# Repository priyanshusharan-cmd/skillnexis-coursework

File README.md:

# SkillNexis Coursework

One repository for all 26 enrolled subjects. Each subject has its own folder, with work grouped under `week-1/` or `week-2/` as available. Course names use lowercase slugs for readable paths.

## Subjects

| Course | Folder |
|---|---|
| C Programming | `c-programming/` |
| C++ Programming | `cpp-programming/` |
| Python Programming | `python/` |
| Java Programming | `java/` |
| Web Development | `web-development/` |
| Full Stack Web Dev (MERN) | `mern/` |
| Data Science with Python | `data-science-python/` |
| Machine Learning & AI | `machine-learning-ai/` |
| Data Structures & Algorithms | `dsa/` |
| Mobile App Dev (Flutter) | `flutter/` |
| Cloud Computing with AWS | `aws-cloud/` |
| Data Analyst | `data-analyst/` |
| Power BI | `power-bi/` |
| Game Developer (Android & iOS) | `game-development/` |
| Software QA Tester (Bug Hunter) | `qa-testing/` |
| UI/UX Designer | `ui-ux/` |
| Digital Marketing | `digital-marketing/` |
| Video Editor & Content Creator | `video-editing/` |
| IoT with AI | `iot/` |
| IoT & C Embedded Programming | `iot-c-embedded/` |
| Educational Content Creator Intern | `educational-content-creator/` |
| 3D Modeling & CAD for Simulation | `3d-cad-design/` |
| AI Automation Engineer | `ai-automation/` |
| Software Engineer | `software-engineer/` |
| Deep Learning & AI | `deep-learning/` |
| Generative AI & LLMs | `generative-ai-llm/` |

## Week 1 status and evidence

Week 1 source packs were available for 20 distinct subjects. The Data Science download duplicated the Data Analyst pack, so its folder labels that source limitation. The other five folders were prepared from their Week 1 requirements on the course site. No downloaded lecture bundles are copied into this repository.

Some deliverables require an environment or evidence that was not available during preparation: AWS account/bucket activity, IoT hardware, a Unity or Flutter build, video footage/export, Figma files, a live demo-site bug report, 3D renders/exports, and model evaluation outputs. Those folders include source, plans, or templates and clearly identify evidence that still needs to be collected. Synthetic datasets are labeled as such. No run or result is claimed unless its evidence is included.

C Programming and Python also contain Week 2 folders from earlier work. Other courses currently contain Week 1 only.

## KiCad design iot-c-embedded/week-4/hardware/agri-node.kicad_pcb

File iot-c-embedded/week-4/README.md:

# IoT & C Embedded Programming — Week 4: Smart Agriculture System (Major Project)

An ESP32 node that watches soil moisture, temperature and light, waters plants through a pump, reports over MQTT, sleeps most of the time to run on one 18650 cell, and updates itself over the air with automatic rollback. Includes a **KiCad PCB** that passes DRC with Gerbers ready to order, a **3D-printable enclosure**, and full documentation.

## Brief checklist

| Requirement | Where | Evidence |
| --- | --- | --- |
| **Two FreeRTOS tasks: sensor reading and display update** | `app/app.c`: **four** tasks. `sensor` (samples, queue), `control` (irrigation state machine, owns the pump, highest priority), `display` (OLED), `net` (MQTT publish/commands). A queue, a mutex around shared status, and an event group for publish/sleep. | Runs on the **real FreeRTOS kernel** (V11.1.0 POSIX port) in CI, and on the ESP32 inside ESP-IDF's FreeRTOS |
| **Deep sleep, wake on button press** | `esp32/main/main.c`: `esp_deep_sleep_start()` with the timer *and* `ext0` wake-up on GPIO25. The button means "water now". State survives in `RTC_DATA_ATTR` memory. | Sleep length is chosen per cycle (5 min near the threshold, 30 min when wet, 2 h on a low battery). Simulation: awake **1.4 %** of the time |
| **OTA firmware updates** | `hal_ota()`: MQTT command `ota=https://...` → `esp_https_ota` into the inactive slot (`partitions.csv`, two 1.9 MB slots), certificate-bundle verified, then reboot. **Rollback**: the new image stays "pending verify" until it reaches the MQTT broker; 3 failed boots roll back to the previous firmware. The pump is switched off before any reboot. | Built in CI; the command path is exercised in the simulation |
| **Documentation with circuit diagrams and flowcharts** | `docs/schematic.png`, `docs/flowchart.png`, `hardware/` (PCB, BOM), this README | Below |
| **Major project: soil moisture, temperature, light, relay pump, OLED, WiFi + MQTT, FreeRTOS, deep sleep, OTA, PCB, enclosure, documentation** | All of the above, plus `hardware/agri-node.kicad_pcb`, `hardware/agri-node-gerbers.zip`, `hardware/enclosure.scad` and `hardware/stl/` | Below |

## Irrigation rules (`common/agri.c`)

| Rule | Why |
| --- | --- |
| Start below **35 %** soil moisture, stop above **60 %** (hysteresis) | Avoids short on/off cycles |
| Each watering lasts at most **300 s** | A stuck probe or a burst pipe can't empty the tank |
| Rest **30 min** between waterings | Water needs time to soak in before the probe reads it |
| **1,200 s per day** budget, reset at midnight; manual watering can't exceed it | Protects the tank and the plants |
| Skip watering above **34 °C** or **85 %** light, unless the soil is critically dry (< 17.5 %) | Midday water mostly evaporates |
| **Tank empty** (float switch): pump locked out, including manual commands; resumes when refilled | Pumps burn out running dry |
| **Probe fault** (reading outside its calibration ±400): locked out until it reads sensibly again | An unplugged probe reads "bone dry" and would flood the bed |

**36 unit tests** (`make test`, ASan + UBSan) cover every rule and edge, including the midnight budget reset, manual override limits and fault recovery. They caught a real bug during development: after a fault cleared, the controller used a stale timer, so recovery behaved differently depending on how long the fault had lasted. It now re-evaluates immediately.

## Firmware simulation: 3 days in about 4 seconds

`sim/` runs the *same* `app/app.c` against a soil/weather model. Days 1 and 3 are hot and sunny, day 2 is cloudy, and the sensors return raw ADC values derived from the model. Two builds:
- `make sim-freertos`: the real **FreeRTOS kernel** (POSIX port, fetched at a pinned release). Runs in CI.
- `make sim`: a small pthread stand-in for the same API (`sim/shim/`) for quick local runs.

| Scripted event | Expected | Result (FreeRTOS, CI) |
| --- | --- | --- |
| Day 2, 14:00–17:00: tank empty | Pump never runs; waters once refilled | PASS (lockout at 14:00, watered at 17:05 just after the refill) |
| Day 3, 02:00–02:30: probe unplugged | Sensor-fault lockout, recovers | PASS |
| Day 3, 07:00: MQTT `water` | Manual watering at the next wake-up | PASS |
| Day 3, 12:00: MQTT `ota=...` | Reaches the OTA handler | PASS |
| Whole run | No watering > 300 s, daily budget never exceeded, ≥ 1 watering/day, asleep > 95 % | PASS: 4 waterings, ~290 s of pumping per day, **awake 1.3–1.45 %** |

On day 1 the soil crosses 35 % around 13:00 but the controller waits out the heat and waters at about 16:40 (chart above; exact minutes vary by a few between runs because of sensor noise). That is the heat rule doing its job.

## Hardware

| | |
| --- | --- |
|  |  |

- **PCB** (`hardware/make_pcb.py` → `agri-node.kicad_pcb`): 85 × 62 mm, 2 layers, generated with KiCad 7's Python API. It carries a 30-pin ESP32 DevKit on sockets. Each sensor has its own straight lane to its GPIO row, GND is poured on both layers with stitching vias, there's a copper keep-out under the antenna, and 0.8 mm tracks carry the battery and pump current. **DRC: 0 errors, 0 unconnected pads** (`python3 hardware/run_drc.py`; only silkscreen-overlap warnings remain). Ready to order: `hardware/agri-node-gerbers.zip` (Gerbers + Excellon drill, JLCPCB/PCBWay compatible).
- **Pump driver**: AO3400A low-side MOSFET (fully on at 2.5 V gate drive, so the ESP32's 3.3 V pin drives it directly), 100 Ω gate resistor, 100 kΩ pull-down so the pump stays off while the ESP32 boots, SS14 flyback diode.
- **Power**: 1S 18650 → ME6211C33 LDO (40 µA quiescent) with 470 µF bulk for WiFi bursts; the DevKit is fed on its 3V3 pin. Battery voltage is sensed through a 100k/100k divider on GPIO33.
- **BOM**: `hardware/BOM.csv`, 25 lines, about ₹2,000 for a complete node.
- **Enclosure** (`hardware/enclosure.scad`, STLs in `hardware/stl/`): 116 × 69 × 34 mm, PETG/ASA. Board standoffs for M3 heat-set inserts, an 18650 cradle, three PG7 cable-gland holes on the bottom face, a vent/drain hole, a lid with lip and gasket groove, an OLED window, and button access.

### Pin map

| ESP32 | Function | | ESP32 | Function |
| --- | --- | --- | --- | --- |
| GPIO34 | Soil probe signal (ADC1_CH6) | | GPIO26 | Pump MOSFET gate |
| GPIO32 | Soil probe power (on only while sampling) | | GPIO27 | Float switch (pull-up) |
| GPIO36 | LDR (ADC1_CH0) | | GPIO25 | Wake/water button (ext0) |
| GPIO33 | Battery ÷ 2 (ADC1_CH5) | | GPIO21/22 | I2C SDA/SCL: BME280 0x76, OLED 0x3C |

## Power budget (`docs/power-budget.md`)

Uses the simulated duty cycle (138 wake-ups/day, ~21 min awake/day, ~290 s of pumping/day) and **datasheet** currents, not measurements:

| Build | mAh/day | Days on one 18650, no sun |
| --- | ---: | ---: |
| Bare ESP32-WROOM module (next PCB revision) | 75 | 34 |
| DOIT DevKit, power LED removed | 97 | 26 |
| DOIT DevKit as bought | 263 | 10 |

A 1 W panel supplies about 800 mAh/day on a 4-sun-hour day, so with a TP4056 charger the node runs indefinitely. The biggest improvement left is in the hardware, not the firmware: the DevKit's USB-UART chip and LED dwarf the ESP32's own 10 µA sleep current.

## Build and run

```sh
make test            # irrigation logic, 36 checks
make sim             # 3-day simulation (pthread stand-in) + chart
make sim-freertos    # same on the real FreeRTOS kernel (clones V11.1.0)
cd esp32 && cp main/secrets.example.h main/secrets.h && pio run -t upload -t monitor
python3 hardware/make_pcb.py && python3 hardware/run_drc.py   # in hardware/
openscad -D 'part="base"' -o base.stl hardware/enclosure.scad
```

MQTT topics: `farm/<node>/state` (retained JSON: soil, temp, humidity, light, battery, pump, tank, state, reason, water used today), `farm/<node>/status` (online/offline last-will), `farm/<node>/cmd` (`water`, `stop`, `ota=<https url>`), `farm/<node>/ota` (update progress).

**Not done here:** no hardware was built. The firmware is compile-checked for the ESP32 in CI, and its logic runs in the simulator. The PCB has not been fabricated. Next: order the boards, assemble, measure real sleep current, and calibrate `raw_dry` / `raw_wet` against your soil.

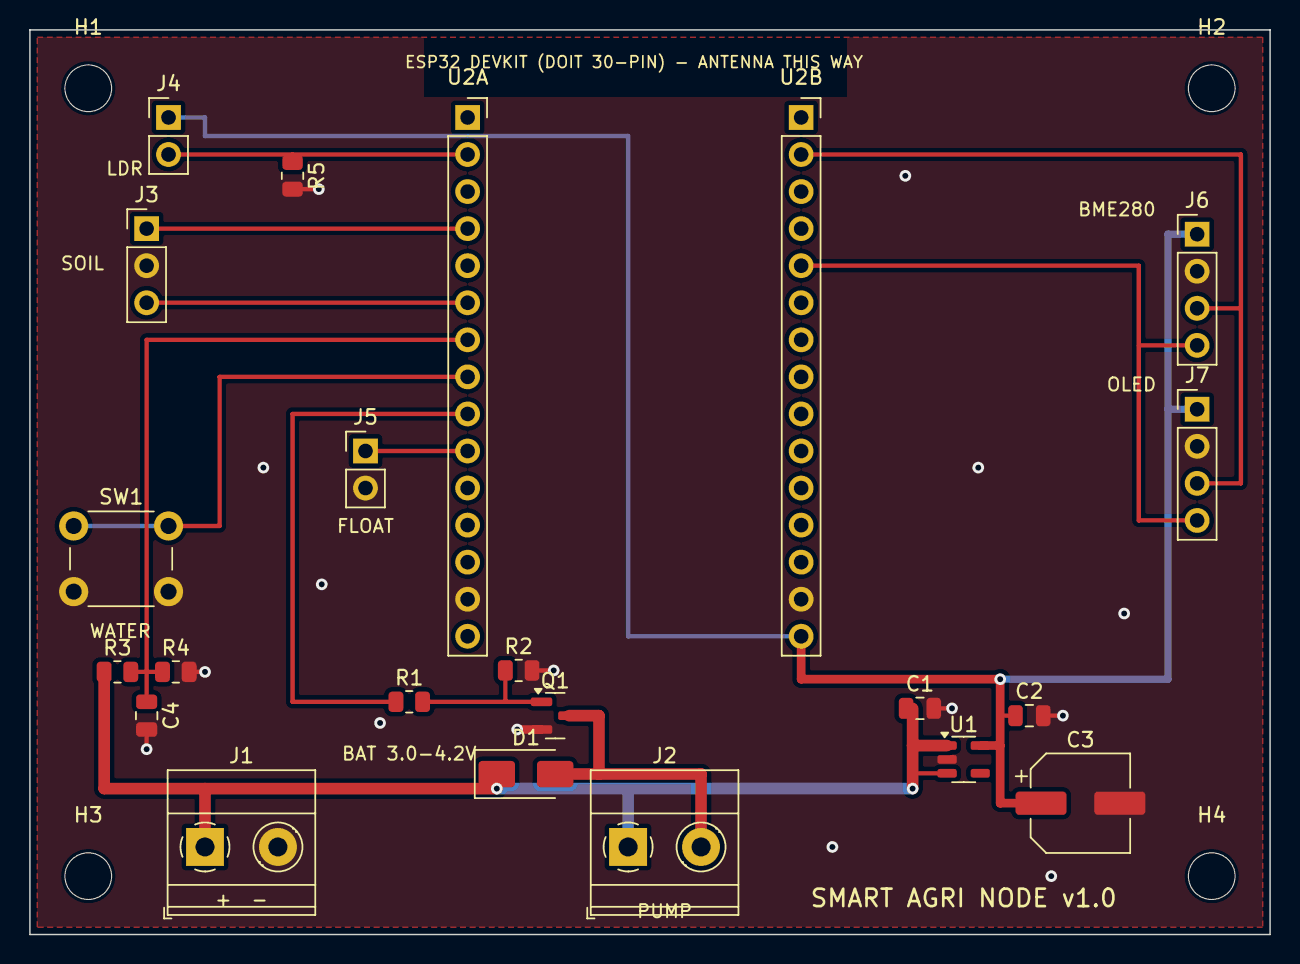
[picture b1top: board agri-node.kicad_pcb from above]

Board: 2 copper layers, 85.0 x 62.0 mm, 26 parts (0 on the bottom side), 14 nets.

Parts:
C1, C2: 10u; C_0805_2012Metric
C3: 470u; CP_Elec_6.3x5.8
C4: 100n; C_0805_2012Metric
D1: SS14; D_SMA
H1, H2, H3, H4: M3; MountingHole_3.2mm_M3
J1: BAT 1S Li-ion; TerminalBlock_Phoenix_MKDS-1,5-2_1x02_P5.00mm_Horizontal
J2: PUMP; TerminalBlock_Phoenix_MKDS-1,5-2_1x02_P5.00mm_Horizontal
J3: SOIL; PinHeader_1x03_P2.54mm_Vertical
J4: LDR; PinHeader_1x02_P2.54mm_Vertical
J5: FLOAT; PinHeader_1x02_P2.54mm_Vertical
J6: BME280; PinHeader_1x04_P2.54mm_Vertical
J7: OLED; PinHeader_1x04_P2.54mm_Vertical
Q1: AO3400A; SOT-23
R1: 100R; R_0805_2012Metric
R2, R3, R4: 100k; R_0805_2012Metric
R5: 10k; R_0805_2012Metric
SW1: WAKE/WATER; SW_PUSH_6mm
U1: ME6211C33; SOT-23-5
U2A: ESP32 DevKit left; PinSocket_1x15_P2.54mm_Vertical
U2B: ESP32 DevKit right; PinSocket_1x15_P2.54mm_Vertical

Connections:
+3V3: C2.1, C3.1, J4.1, J6.1, J7.1, U1.5, U2B.15
BAT+: C1.1, D1.1, J1.1, J2.1, R3.1, U1.1, U1.3
GATE: Q1.1, R1.2, R2.1
GND: C1.2, C2.2, C3.2, C4.2, J1.2, J3.2, J5.2, J6.2, J7.2, Q1.2, R2.2, R4.2, R5.2, SW1.2, U1.2, U2A.14, U2B.14
IO25: SW1.1, U2A.8
IO26: R1.1, U2A.9
IO27: J5.1, U2A.10
IO32: J3.3, U2A.6
IO33: C4.1, R3.2, R4.1, U2A.7
IO34: J3.1, U2A.4
IO36: J4.2, R5.1, U2A.2
PUMP-: D1.2, J2.2, Q1.3
SCL: J6.3, J7.3, U2B.2
SDA: J6.4, J7.4, U2B.5

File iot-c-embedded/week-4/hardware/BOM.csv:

Ref,Qty,Part,Value / MPN,Footprint,Notes,Approx price (INR)
U2,1,ESP32 DevKit,DOIT ESP32 DevKit V1 (30-pin),2x PinSocket 1x15 2.54 mm,Plugs into sockets; remove its power LED for battery use,350
U1,1,LDO 3.3 V 500 mA,ME6211C33M5G (or AP2112K-3.3),SOT-23-5,Low quiescent current (40 uA),15
Q1,1,N-MOSFET logic-level,AO3400A,SOT-23,30 V / 5.7 A; Rds(on) < 50 mOhm at Vgs 2.5 V,5
D1,1,Schottky flyback diode,SS14,SMA,Across the pump,3
R1,1,Resistor,100 Ohm,0805,Gate series,1
R2,1,Resistor,100k,0805,Gate pull-down: pump stays off while the ESP32 boots,1
R3 R4,2,Resistor,100k 1%,0805,Battery divider (VBAT/2),2
R5,1,Resistor,10k,0805,LDR divider,1
C1 C2,2,Ceramic capacitor,10 uF 10 V X5R,0805,LDO in/out,4
C3,1,Electrolytic capacitor,470 uF 6.3 V,CP_Elec_6.3x5.8,Covers WiFi current bursts,8
C4,1,Ceramic capacitor,100 nF,0805,ADC filter on the divider,1
SW1,1,Tactile switch,6x6 mm THT,SW_PUSH_6mm,Wake / water now,3
J1 J2,2,Screw terminal,Phoenix MKDS 1.5/2 (5.00 mm),TerminalBlock_Phoenix,Battery in / pump out,20
J3,1,Pin header,1x03 2.54 mm,PinHeader_1x03,Capacitive soil probe v1.2,2
J4 J5,2,Pin header,1x02 2.54 mm,PinHeader_1x02,LDR / float switch,2
J6 J7,2,Pin header,1x04 2.54 mm,PinHeader_1x04,BME280 / SSD1306 OLED,3
-,1,Capacitive soil moisture sensor,v1.2 (corrosion-resistant),-,-,80
-,1,BME280 module,I2C 0x76,-,-,250
-,1,SSD1306 OLED 0.96 in,I2C 0x3C,-,-,180
-,1,Float switch,Vertical PP,-,Normally closed when water present,60
-,1,LDR,GL5528,-,-,5
-,1,Mini submersible pump,3-6 V DC,-,With silicone tubing,120
-,1,18650 cell + holder,3000 mAh protected,-,-,250
-,1,Solar charger,TP4056 + DW01 module + 1 W 6 V panel,-,-,200
-,1,PCB,85 x 62 mm 2-layer 1.6 mm,-,JLCPCB / PCBWay: 5 pcs,450
